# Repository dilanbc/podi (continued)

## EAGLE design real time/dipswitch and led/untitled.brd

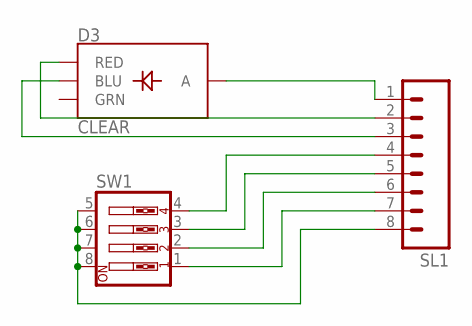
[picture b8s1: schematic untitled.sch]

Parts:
D3: CLEAR; LED-RGB-THRU
SL1: M08; 08P
SW1: SW_DIP-4; EDG-04

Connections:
unnamed: D3.2 (A), SL1.1
unnamed: D3.1 (RED), SL1.2
unnamed: D3.4 (BLU), SL1.3
unnamed: SL1.4, SW1.4
unnamed: SL1.5, SW1.3
unnamed: SL1.6, SW1.2
unnamed: SL1.7, SW1.1
unnamed: SL1.8, SW1.5, SW1.6, SW1.7, SW1.8

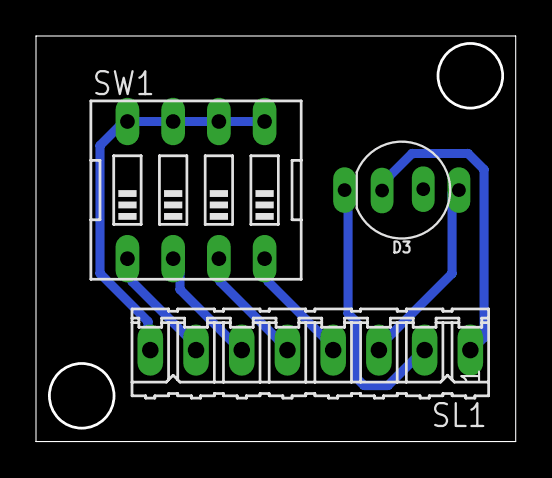
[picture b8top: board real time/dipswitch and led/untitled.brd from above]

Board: 2 copper layers, 26.6 x 22.5 mm, 3 parts (0 on the bottom side), 8 nets.
